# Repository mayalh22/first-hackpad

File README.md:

# First Hackpad

This is my first hackpad project, made following the Blueprint Hackpad Tutorial.

---

## Overview

A simple 4-key macropad using the Seeed XIAO RP2040 and MX-style switches.  

---

## Schematic

*Schematic of the hackpad.*

---

## PCB

*PCB layout.*

---

## Case

*Case for the hackpad.*

---

## Parts Used

- Seeed XIAO RP2040  
- MX-style switches  

---

## Notes

Used the starter code from the tutorial. No extra features or customization added.

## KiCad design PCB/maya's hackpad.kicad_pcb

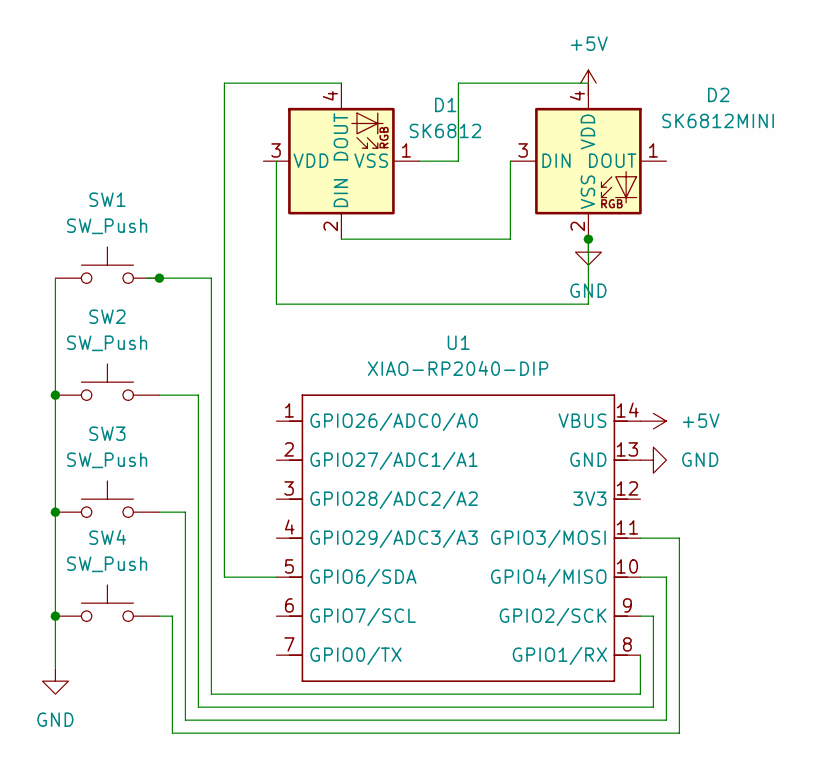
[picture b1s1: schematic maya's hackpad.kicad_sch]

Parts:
D1: SK6812; LED_SK6812MINI_PLCC4_3.5x3.5mm_P1.75mm
D2: SK6812MINI; LED_SK6812MINI_PLCC4_3.5x3.5mm_P1.75mm
SW1, SW2, SW3, SW4: SW_Push; SW_Cherry_MX_1.00u_PCB
U1: XIAO-RP2040-DIP; MOUDLE14P-XIAO-DIP-SMD

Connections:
+5V: U1.14 (VBUS)
GND: D2.2 (VSS), SW1.1, SW2.1, SW3.1, SW4.1, U1.13 (GND)
unnamed: D1.2 (DIN), D2.3 (DIN)
unnamed: D1.4 (DOUT), U1.5 (GPIO6/SDA)
unnamed: D1.1 (VSS), D2.4 (VDD)
unnamed: SW1.2, U1.8 (GPIO1/RX)
unnamed: SW2.2, U1.9 (GPIO2/SCK)
unnamed: SW4.2, U1.11 (GPIO3/MOSI)
unnamed: SW3.2, U1.10 (GPIO4/MISO)

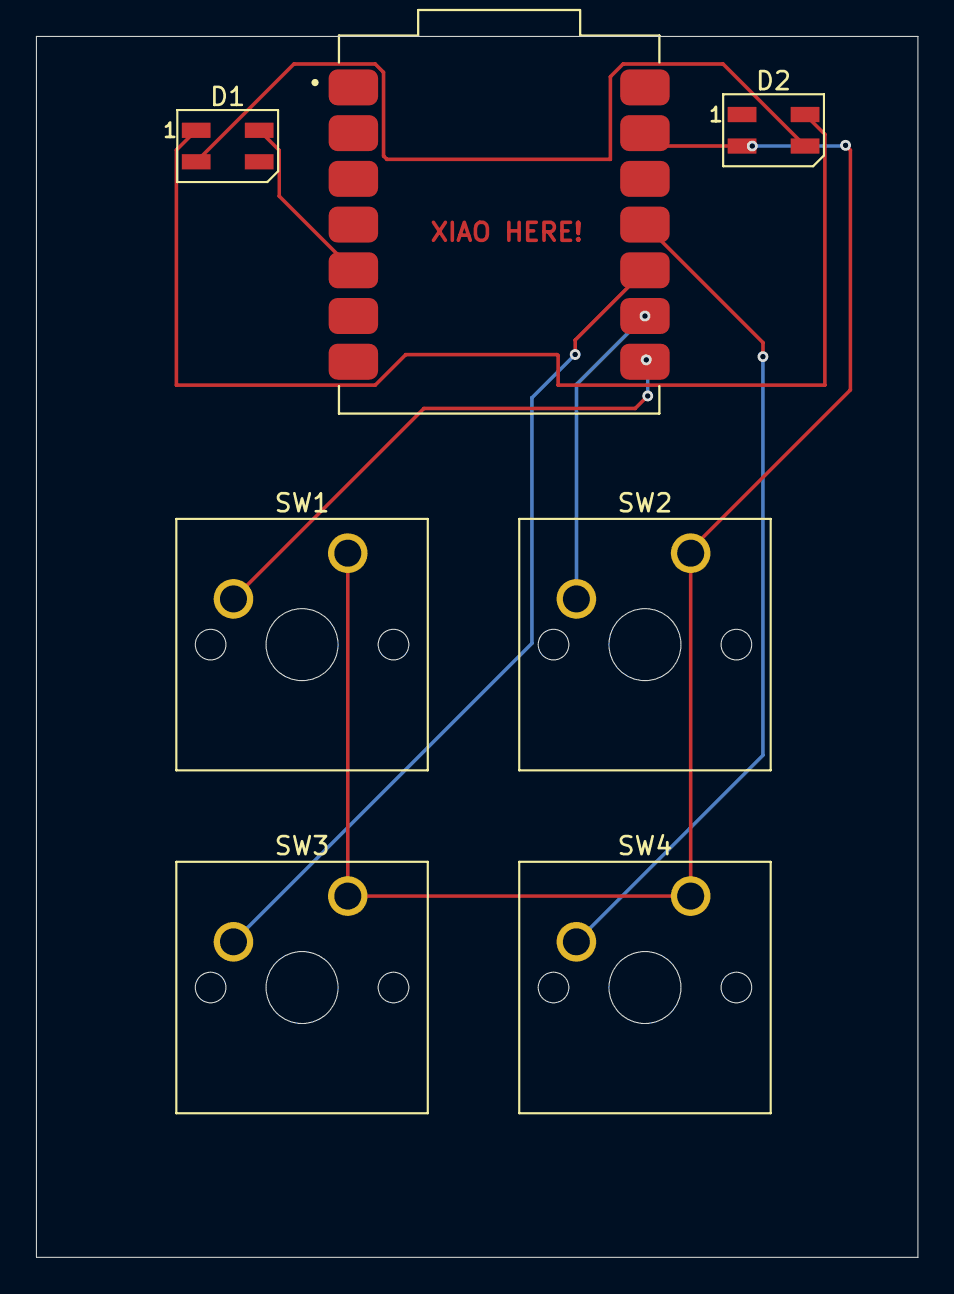
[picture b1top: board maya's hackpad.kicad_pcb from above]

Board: 2 copper layers, 49.0 x 67.8 mm, 7 parts (0 on the bottom side), 8 nets.

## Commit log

2025-12-28 added starter code
2025-12-28 added readme and screenshots
2025-12-28 updated image paths
2025-12-29 added timer firmware
